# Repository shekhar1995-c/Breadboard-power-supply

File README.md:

# Breadboard Power Supply (5V / 3.3V) — KiCad Project

A beginner-friendly breadboard power supply PCB design (5V selectable / 3.3V) created in KiCad 6/7/9.

## Contents
- `project_files/` — KiCad schematic & PCB files
- `gerbers/` — gerber files for fabrication (ZIP)
- `bom/` — Bill of Materials and pick-and-place
- `docs/` — screenshots, 3D renders, thumbnails
- `hardware/` — assembly notes & test procedure

## Features
- Input: 9–12V DC (barrel jack)
- Outputs: Selectable 5V or 3.3V via jumper
- Input fuse, power LED, regulator indicators
- AMS1117 regulators (changeable to switching regulator for >500 mA)
- KiCad project + gerbers included

## How to open
1. Install KiCad (https://kicad.org)  
2. Open `project_files/power_supply.kicad_pro`

## Build & Test
- Generate Gerber files from KiCad: `File → Fabrication Outputs → Gerbers`
- Assemble using BOM in `bom/bom.csv`
- Power up with a current-limited bench supply and verify rails with a multimeter

## License
This project is licensed under the MIT License — see `LICENSE`.

## Contributing
PRs and issues welcome. Please include changes to BOM or schematic with a short explanation.

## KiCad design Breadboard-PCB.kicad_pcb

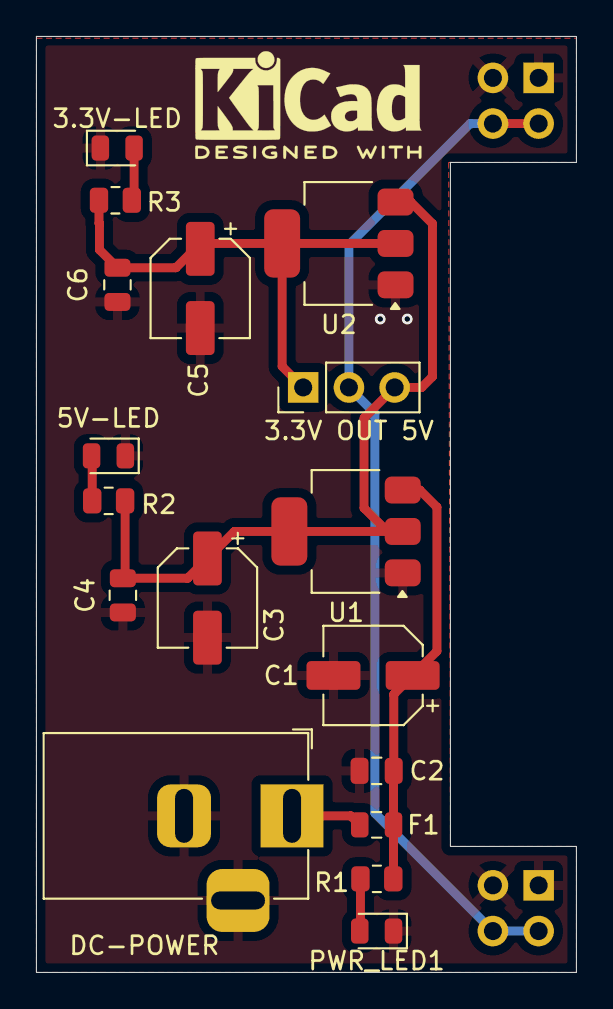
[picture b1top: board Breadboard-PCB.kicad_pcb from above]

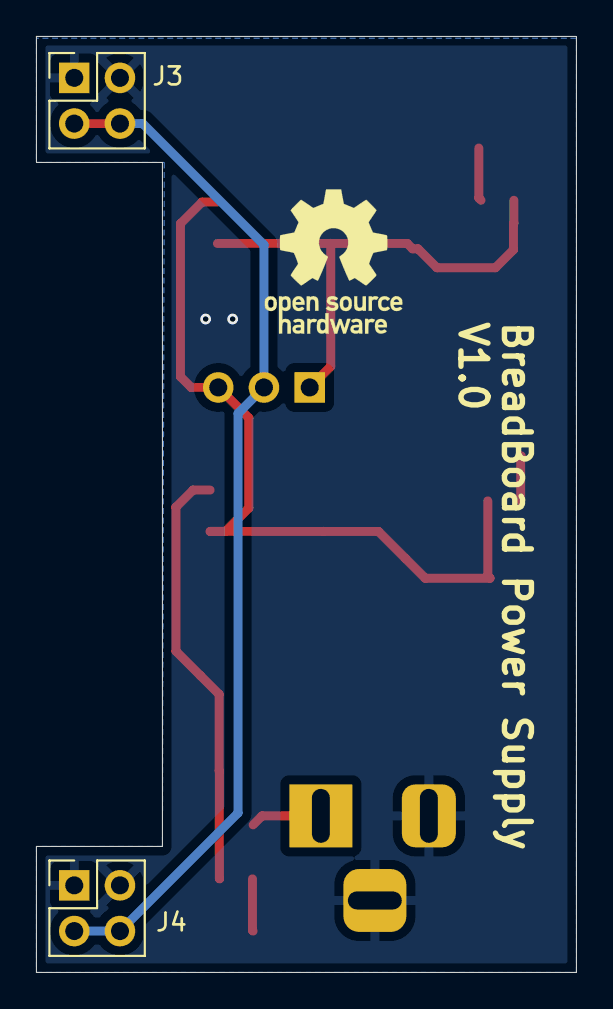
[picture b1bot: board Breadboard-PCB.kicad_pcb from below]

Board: 2 copper layers, 30.0 x 52.0 mm, 19 parts (2 on the bottom side), 9 nets.

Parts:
3.3V OUT 5V: Conn_01x03_Pin; PinHeader_1x03_P2.54mm_Vertical
3.3V-LED, 5V-LED: GREEN_LED; LED_0805_2012Metric
C1, C3, C5: 100uF; CP_Elec_5x5.8
C2, C4, C6: 0.1uf; C_0805_2012Metric
DC-POWER: Barrel_Jack_Switch; BarrelJack_Horizontal
F1: Fuse; Fuse_0805_2012Metric
J3, J4: Conn_02x02_Odd_Even; PinHeader_2x02_P2.54mm_Vertical
PWR_LED1: GREEN_LED; LED_0805_2012Metric
R1: 1k; R_0805_2012Metric
R2: 560; R_0805_2012Metric
R3: 330; R_0805_2012Metric
U1: AMS1117-5.0; SOT-223-3_TabPin2
U2: AMS1117-3.3; SOT-223-3_TabPin2

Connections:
/3.3V: 3.3V OUT 5V.1, C5.1, C6.1, R3.1, U2.2 (VO)
/5V: 3.3V OUT 5V.3, C3.1, C4.1, R2.1, U1.2 (VO), U2.3 (VI)
/V_OUT: 3.3V OUT 5V.2, J3.3, J3.4, J4.3, J4.4
GND: 3.3V-LED.1 (K), 5V-LED.1 (K), C1.2, C2.2, C3.2, C4.2, C5.2, C6.2, DC-POWER.2, DC-POWER.3, J3.1, J3.2, J4.1, J4.2, PWR_LED1.1 (K), U1.1 (GND), U2.1 (GND)
unnamed: 3.3V-LED.2 (A), R3.2
unnamed: 5V-LED.2 (A), R2.2
unnamed: DC-POWER.1, F1.1
unnamed: PWR_LED1.2 (A), R1.2
unnamed: C1.1, C2.1, F1.2, R1.1, U1.3 (VI)

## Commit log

2025-11-08 Initial commit — KiCad breadboard power supply project
